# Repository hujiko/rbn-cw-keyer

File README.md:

# RBN CW Keyer

This project involves using an Arduino to send predefined text as Morse code to reach the Reverse Beacon Network (RBN). The RBN is a network of radio stations worldwide that listen for Morse code signals and report the frequency, speed, and signal strength of the transmitted signals.

## Features

- Sends predefined text messages as Morse code using an Arduino.
- Configurable Morse code speed.
- Simple and easy-to-understand Arduino code.
- Easily extendable for custom text messages.

## Hardware Requirements

- Arduino Nano Board
- the CW keyer PCB or a breadboard installation
- 2 Optocouplers (e.g. EL817)
- 2 Resistors (~160 Ohm)
- (optional) 2 LEDs and matching resistors.

## Hardware setup

Solder the components to the PCB as instructed, or rebuild the circuit on a breadboard following the schematic in the `cw-keyer-hardware` directory. You need the free software `KiCAD` to open the schematic.

## Software setup (VSCode & PlatformIO)

Download the repository to your local machine and open VSCode. In the left side, there should be an icon looking like an alien-head. Click that to open the PlatformIO quick access menu. In there, click "Open", and in the then opened PlatformIO interface "Open Project". Navigate to the downloaded files and select the "microcontroller-software" subdirectory.

In the small bottom bar of PlatformIO you should now see a row of icons: A house, a checkmark, an arrow pointing right, a trash can, ...

Click the "Checkmark" icon. This will start compiling the source code. it should open a small terminal within PlatformIO and after 1-2 seconds, a green SUCCESS should indicate a successful compilation. Now connect your Arduino with a USB-Cable to your computer and in PlatformIO click the icon of an arrow pointing right. This should upload the project to your microcontroller. When doing that, you can either remove the microcontroller from the PCB, or leave it in. Both works completely fine.

Expect to see a green "SUCCESS" at least for "nanoatmega168". Don't worry if you see an error for "attiny85". As stated in the very beginning: We decided against using this microcontroller, as the financial benefit was not worth the limitations it brings.

## Change the text to be transmitted

in `microcontroller-software/src/main.cpp` change the `text` variable to what you want to be transmitted.

## Change the WPM speed

Currently the speed has to be set in milliseconds. For 25 WPM, use 52ms. For 13 WPM, use 90ms.

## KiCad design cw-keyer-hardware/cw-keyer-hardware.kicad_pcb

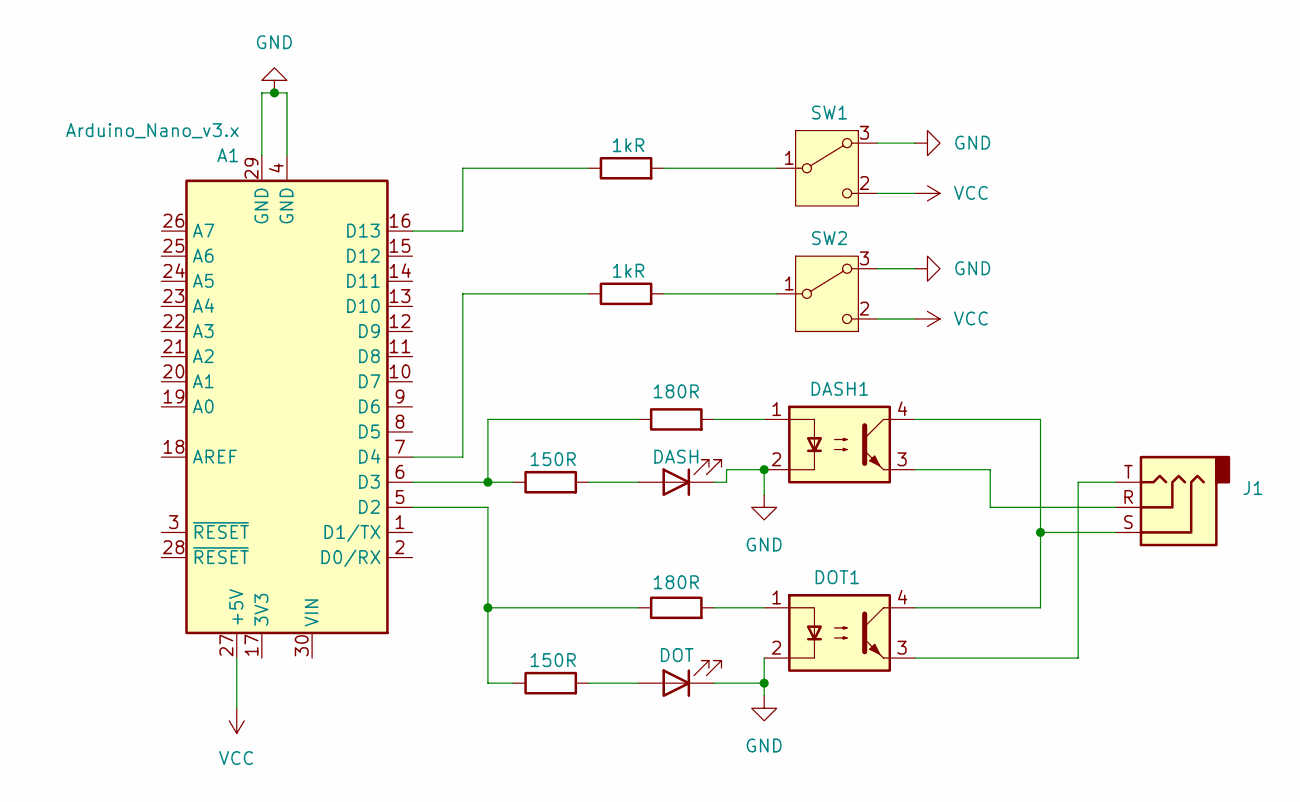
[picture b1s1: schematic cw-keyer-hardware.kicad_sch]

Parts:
A1: Arduino_Nano_v3.x; Arduino_Nano
D1: DASH; LED_0805_2012Metric_Pad1.15x1.40mm_HandSolder
D2: DOT; LED_0805_2012Metric_Pad1.15x1.40mm_HandSolder
DASH1: EL817; SMDIP-4_W7.62mm
DOT1: EL817; SMDIP-4_W7.62mm
J1: AudioJack3; Jack_3.5mm_CUI_SJ1-3523N_Horizontal
R1, R2: 180R; R_0805_2012Metric_Pad1.20x1.40mm_HandSolder
R3, R4: 150R; R_0805_2012Metric_Pad1.20x1.40mm_HandSolder
R5, R6: 1kR; R_0805_2012Metric_Pad1.20x1.40mm_HandSolder
SW1, SW2: SW_Wuerth_450301014042; SW_Slide-03_Wuerth-WS-SLTV_10x2.5x6.4_P2.54mm

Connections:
GND: A1.4 (GND), A1.29 (GND), D1.1 (K), D2.1 (K), DASH1.2, DOT1.2, SW1.3 (A), SW2.3 (A)
unnamed: A1.5 (D2), R2.1, R3.1
unnamed: A1.6 (D3), R1.1, R4.1
unnamed: A1.7 (D4), R6.1
unnamed: A1.16 (D13), R5.1
unnamed: D1.2 (A), R4.2
unnamed: D2.2 (A), R3.2
unnamed: DASH1.1, R1.2
unnamed: DASH1.3, J1.R
unnamed: DASH1.4, DOT1.4, J1.S
unnamed: DOT1.1, R2.2
unnamed: DOT1.3, J1.T
unnamed: R5.2, SW1.1 (B)
unnamed: R6.2, SW2.1 (B)
VCC: A1.27 (+5V), SW1.2 (C), SW2.2 (C)

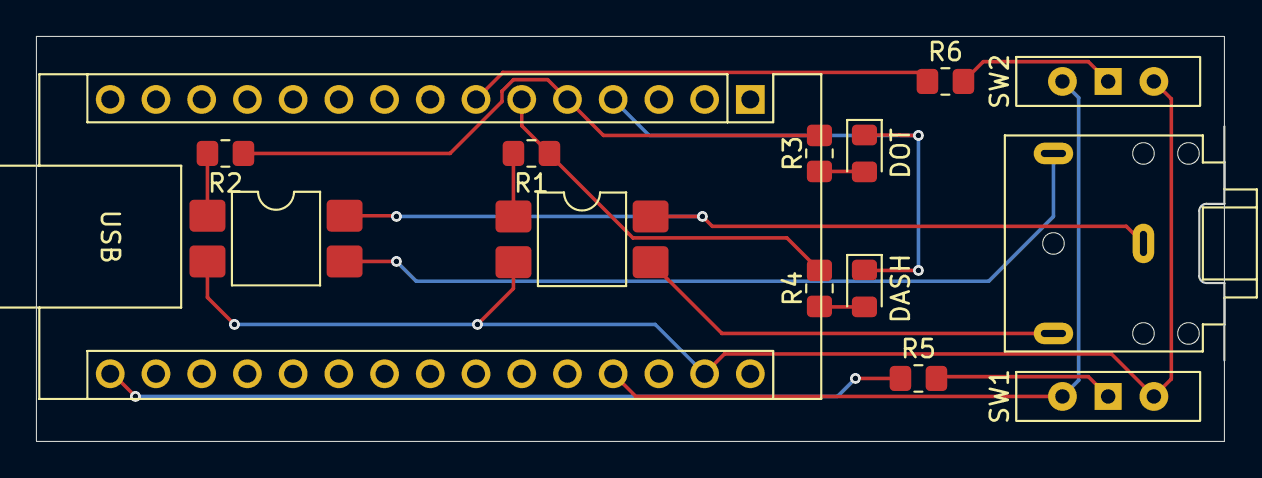
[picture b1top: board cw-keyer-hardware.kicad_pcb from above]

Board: 2 copper layers, 66.0 x 22.5 mm, 14 parts (0 on the bottom side), 15 nets.

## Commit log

2025-06-18 Initial commit - Version 0.1
